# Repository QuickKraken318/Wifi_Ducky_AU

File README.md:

Original project: https://github.com/spacehuhn/wifi_ducky

Tried and tested with a transplanted ATMEGA32U4-AU

The ESP8266 was flashed with a external flasher before getting soldered to the pcb

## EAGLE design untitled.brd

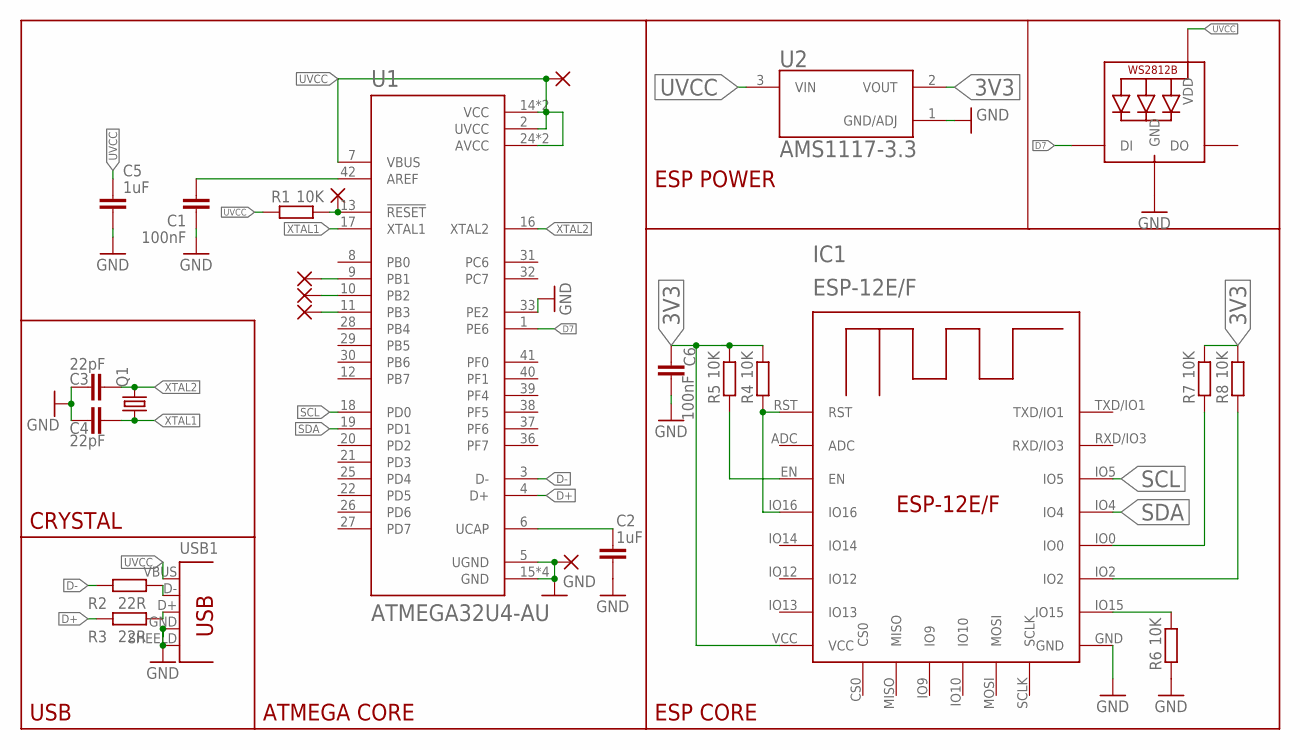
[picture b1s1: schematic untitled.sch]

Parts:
C1, C6: 100nF; C0805
C2, C5: 1uF; C0805
C3, C4: 22pF; C0805
IC1: ESP-12E/F; ESP-12E
LED1: WS2812B5050; WS2812B
PAD1, PAD2, PAD3, PAD4, PAD5, PAD6: 1,6/0,8
Q1: CRYSTALCTS406; CTS406
R1, R4, R5, R6, R7, R8: 10K; R0805
R2, R3: 22R; R0805
U1: ATMEGA32U4-AU; QFP80P1200X1200X120-44N
U2: AMS1117-3.3; SOT229P700X180-4N
USB1: TYPE-A-MALE-SHILED; TYPE-A-MALE

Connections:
3V3: C6.1, IC1.VCC, R4.2, R5.2, R7.2, R8.2, U2.2 (VOUT)
D7: LED1.4-DIN (DI), U1.1 (PE6)
D+: R3.1, U1.4 (D+)
D-: R2.1, U1.3 (D-)
GND: C1.1, C2.2, C3.1, C4.1, C5.2, C6.2, IC1.GND, LED1.3-GND (GND), PAD6.1, R6.1, U1.5 (UGND), U1.15 (GND), U1.23 (GND), U1.33 (PE2), U1.35 (GND), U1.43 (GND), U2.1 (GND/ADJ), USB1.GND (4), USB1.SHEELD (5)
MISO: PAD3.1, U1.11 (PB3)
MOSI: PAD2.1, U1.10 (PB2)
unnamed: R2.2, USB1.D- (2)
unnamed: C1.2, U1.42 (AREF)
unnamed: C2.1, U1.6 (UCAP)
unnamed: R3.2, USB1.D+ (3)
unnamed: IC1.IO16, IC1.RST, R4.1
unnamed: IC1.EN, R5.1
unnamed: IC1.IO0, R7.1
unnamed: IC1.IO2, R8.1
unnamed: IC1.IO15, R6.2
RST: PAD4.1, R1.2, U1.13 (!RESET)
SCK: PAD1.1, U1.9 (PB1)
SCL: IC1.IO5, U1.18 (PD0)
SDA: IC1.IO4, U1.19 (PD1)
UVCC: C5.1, LED1.1-VDD (VDD), PAD5.1, R1.1, U1.2 (UVCC), U1.7 (VBUS), U1.14 (VCC), U1.24 (AVCC), U1.34 (VCC), U1.44 (AVCC), U2.3 (VIN), USB1.VBUS (1)
XTAL1: C4.2, Q1.1, U1.17 (XTAL1)
XTAL2: C3.2, Q1.3 (2), U1.16 (XTAL2)

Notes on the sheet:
CRYSTAL
USB
ATMEGA CORE
ESP POWER
ESP CORE

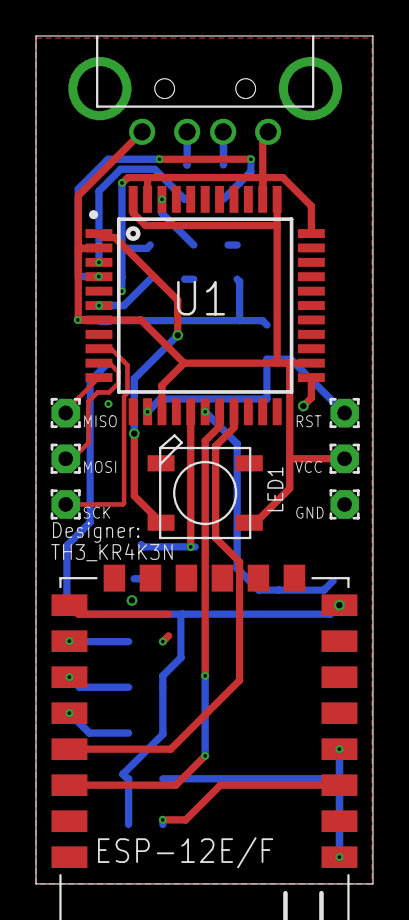
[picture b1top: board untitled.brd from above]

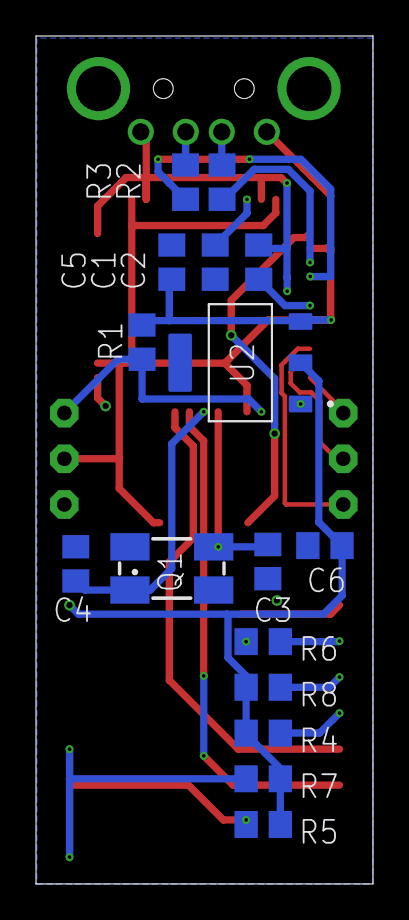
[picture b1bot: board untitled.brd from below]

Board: 2 copper layers, 18.7 x 47.1 mm, 26 parts (16 on the bottom side), 23 nets.
